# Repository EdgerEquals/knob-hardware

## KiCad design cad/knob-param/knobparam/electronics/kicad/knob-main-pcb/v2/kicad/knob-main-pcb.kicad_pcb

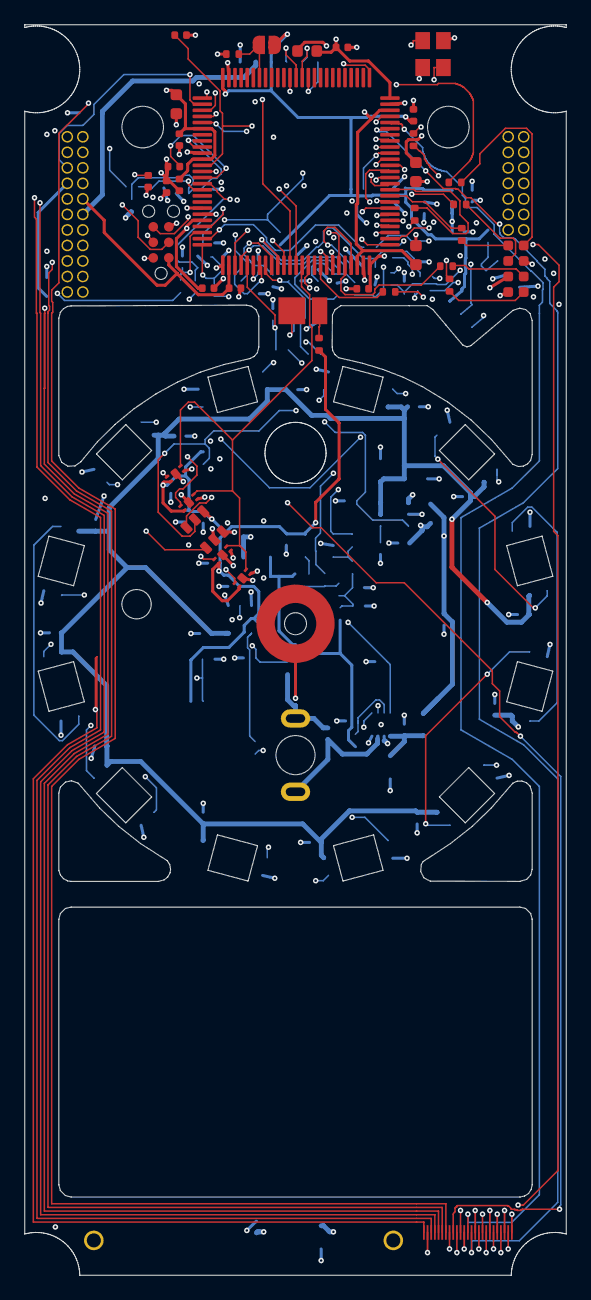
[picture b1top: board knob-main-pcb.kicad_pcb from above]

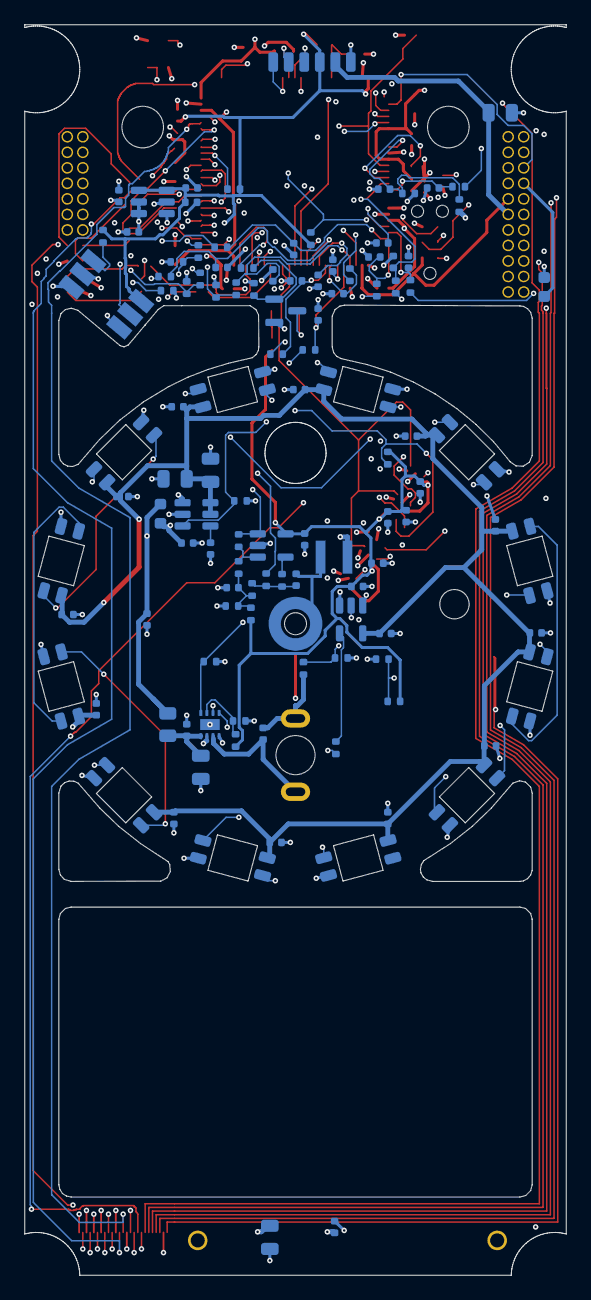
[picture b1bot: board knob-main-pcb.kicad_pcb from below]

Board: 6 copper layers, 44.3 x 102.3 mm, 156 parts (114 on the bottom side), 118 nets.

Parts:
C1, C2, C3, C4, C5, C10, C11, C12, C16, C18, C25, C27, C29, C31, C33, C44, C45, C46, C47, C48, C49, C50, C51, C52, C53, C54, C55, C56, C59, C60: 100nF; C_0402_1005Metric
C6, C64: 10uF; C_0603_1608Metric
C7, C8: 2.2uF; C_0603_1608Metric
C9, C15, C17, C40, C57: 1uF; C_0402_1005Metric
C13, C14: 15pF C0G; C_0402_1005Metric
C19, C20, C21, C22, C23, C24, C26, C28, C30, C32, C37, C38, C39, C41, C65: 1nF C0G; C_0402_1005Metric
C34, C36, C58: 100nF 16V; C_0402_1005Metric
C35, C42, C43, C63: 22uF 16V; C_0805_2012Metric
C61: 10uF 25V; C_0805_2012Metric
C62: 100nF 50V; C_0402_1005Metric
D1, D2, D3, D4, D5, D6, D7, D8, D9, D10, D11, D12: SK6812MINI-E; LED_SK6812MINI-E_Reverse
D13: JNJ-V-2835CW-665003-S-D1; LED_PLCC_2835
FB1: FCM1608KF-601T03; L_0603_1608Metric
FB2: BLM18KG121TZ1D; L_0603_1608Metric
H1: TubeRodClamp_M1.6; TubeRodClamp_Main_M1.6
J1: link flex pads; LinkFlex_MainBoard_Pads_25x0.3
J2: board L header 2x11 1.27 THT; VBoard_L_Header_2x11_P1.27_THT
J3: board R header 2x11 1.27 hybrid; VBoard_R_Header_2x11_P1.27_Hybrid
J4: TC2030-IDC-NL; Tag-Connect_TC2030-IDC-NL_2x03_P1.27mm_Vertical
J5: cover board pads; Pads_1x6_P1.27_SMD
JP1: BOOT0 to 3V3 (bridge to start the ROM bootloader); SolderJumper-2_P1.3mm_Open_RoundedPad1.0x1.5mm
L1: NR3015T470M; L_Taiyo-Yuden_NR-30xx
M1: 1220 coreless planetary, 6 V (hand-solder); Motor_1220_Tabs_Relief
MP1: post GND; Post_Pin_1.0
MP2: post VSYS; Post_Pin_1.0
Q1: 2N7002; SOT-23
R1, R23, R25, R26, R34, R40, R41, R42: 10k; R_0402_1005Metric
R2, R3, R38: 33R; R_0402_1005Metric
R4, R5, R6, R7, R8, R18, R19, R20, R21, R22, R27, R28, R33, R39, R47: 100R; R_0402_1005Metric
R9: 1M; R_0402_1005Metric
R10, R11, R44: 4.7k; R_0402_1005Metric
R12, R13, R14, R15, R16, R17: 22R; R_0402_1005Metric
R24, R46: 220R; R_0402_1005Metric
R29: 0R; R_0805_2012Metric
R30, R31: 0R; R_0402_1005Metric
R32: 3.3k 1%; R_0402_1005Metric
R35: 15k; R_0402_1005Metric
R36: 10k 1%; R_0402_1005Metric
R37, R48, R49: 100k; R_0402_1005Metric
R43: 1k; R_0402_1005Metric
R45: 47k; R_0402_1005Metric
R50: 27k; R_0402_1005Metric
RT1: 10k NTC B3380; R_0402_1005Metric
U1: STM32H743VIT6; LQFP-100_14x14mm_P0.5mm
U2: REF3430IDBVR; SOT-23-6
U3, U4, U5, U6: TMAG5253BA3IQDMRR; X2SON-4_TMAG5253
U7: TMAG5273A2QDBVR; SOT-23-6_TMAG5273_Tight
U8: EE-SX1321; Omron_EE-SX1321
U9: DRV8213DSGR; WSON-8-1EP_2x2mm_P0.5mm_EP0.9x1.6mm
U10: TPS22918DBVR; SOT-23-6
U11: SN74AHCT1G125DBVR; SOT-23-5
U12: TLV3601DBVR; SOT-23-5
Y1: 25MHz 12pF; Crystal_SMD_3225-4Pin_3.2x2.5mm

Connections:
3V3: C1.1, C2.1, C3.1, C4.1, C5.1, C6.1, C11.1, C15.1, C16.1, C25.1, C27.1, C29.1, C31.1, C33.1, C60.1, C64.1, FB1.1, J2.13, J2.15, J2.16, J3.20, J4.1, J5.4, JP1.2, R10.1, R11.1, R23.1, R24.1, R31.2, R36.1, R40.1, R46.1, U1.6, U1.11, U1.27, U1.50, U1.75, U1.100, U2.3, U2.4, U3.1, U4.1, U5.1, U6.1, U7.4, U8.6, U12.5
5V: C57.1, C63.1, FB2.1, J2.7, J2.9, J2.10, J2.11, J3.19, J5.5, L1.1, R29.1
5V_EN: J2.18, U1.2
AGND_SENSE: C23.1, R8.2, U1.29
AGND_SENSE_L: J1.24, R8.1, R9.1
AUDIO_IN: C22.1, R7.2, U1.24
AUDIO_IN_L: J1.22, R7.1
AUDIO_OUT: J1.20, U1.28
BOOT0: JP1.1, R1.1, U1.94
BUS_PRESENT: C65.1, R49.2, R50.1, U1.9
CAN_RX: J3.16, U1.51
CAN_STBY: J3.17, U1.68
CAN_TX: J3.15, U1.52
COVER_EN: J5.3, U1.88
COVER_RX: J5.2, U1.87
COVER_TX: J5.1, U1.86
CS_DAC: J1.4, U1.37
CS_OLED: J1.5, U1.38
CV_IN1: C19.1, R4.2, U1.35
CV_IN1_L: J1.16, R4.1
CV_IN2: C20.1, R5.2, U1.34
CV_IN2_L: J1.17, R5.1
CV_IN3: C21.1, R6.2, U1.33
CV_IN3_L: J1.18, R6.1
DIAL_BUS: C58.2, R39.2, R42.1, R43.1
DIAL_CMN: R43.2, U12.4
DIAL_CMP: R44.2, R45.2, U12.3
DIAL_MID: C59.1, R40.2, R41.1, R42.2, R44.1
DIAL_RX: R45.1, U1.44, U12.1
DIAL_TX: R39.1, U1.43
ENC_A: R27.2, U1.63
ENC_A_L: R25.1, R27.1, U8.5
ENC_B: R28.2, U1.64
ENC_B_L: R26.1, R28.1, U8.4
ENC_LED: R24.2, U8.1
GAINSEL: R30.1, R31.1, U9.7
GND: C1.2, C2.2, C3.2, C4.2, C5.2, C6.2, C7.2, C8.2, C9.2, C10.2, C11.2, C12.2, C13.2, C14.2, C15.2, C16.2, C17.2, C18.2, C19.2, C20.2, C21.2, C22.2, C23.2, C24.2, C25.2, C26.2, C27.2, C28.2, C29.2, C30.2, C31.2, C32.2, C33.2, C34.2, C35.2, C37.2, C38.2, C39.2, C40.2, C41.2, C42.2, C43.2, C44.2, C45.2, C46.2, C47.2, C48.2, C49.2, C50.2, C51.2, C52.2, C53.2, C54.2, C55.2, C56.2, C57.2, C59.2, C60.2, C61.2, C62.2, C63.2, C64.2, C65.2, D1.3, D2.3, D3.3, D4.3, D5.3, D6.3, D7.3, D8.3, D9.3, D10.3, D11.3, D12.3, H1.1, J1.2, J1.12, J1.15, J1.19, J1.21, J1.23, J1.25, J2.2, J2.4, J2.6, J2.8, J2.12, J2.14, J2.17, J2.19, J2.21, J2.22, J3.1, J3.3, J3.6, J3.9, J3.14, J3.18, J3.21, J3.22, J4.5, J5.6, MP1.1, Q1.2, R1.2, R9.2, R25.2, R26.2, R30.2, R32.2, R35.2, R37.2, R41.2, R48.2, R50.2, RT1.2, U1.10, U1.19, U1.26, U1.49, U1.74, U1.99, U2.1, U2.2, U3.2, U3.5, U4.2, U4.5, U5.2, U5.5, U6.2, U6.5, U7.2, U7.3, U8.2, U8.3, U9.4, U9.9, U10.2, U11.1, U11.3, U12.2, Y1.2, Y1.4
HALL1: C26.1, R19.2, U1.32
HALL1_L: R19.1, U3.4
HALL2: C28.1, R20.2, U1.25
HALL2_L: R20.1, U4.4
HALL3D_INT: R23.2, U1.40, U7.5
HALL4: C30.1, R21.2, U1.23
HALL4_L: R21.1, U5.4
HALL5: C32.1, R22.2, U1.15
HALL5_L: R22.1, U6.4
HALL_EN: U1.39, U3.3, U4.3, U5.3, U6.3
HSE_IN: C13.1, U1.12, Y1.1
HSE_OUT: C14.1, U1.13, Y1.3
I2C_SCL: J1.8, R10.2, U1.67, U7.1
I2C_SDA: J1.9, R11.2, U1.66, U7.6
IO_INT: J1.10, U1.54
IPROPI: R32.1, R33.1, U9.8
JOY_LADDER: C24.1, R18.2, U1.16
JOY_LADDER_L: J2.20, R18.1
JOY_PWR_EN: J3.13, U1.65
JOY_QSPI_CLK: R12.1, U1.36
JOY_QSPI_IO0: R14.1, U1.58
JOY_QSPI_IO1: R15.1, U1.59
JOY_QSPI_IO2: R16.1, U1.1
JOY_QSPI_IO3: R17.1, U1.60
JOY_QSPI_NCS: R13.1, U1.46
JOY_RST: J3.11, U1.57
JOY_TE: J3.12, U1.56
LIGHT_A: D13.2, R46.2
LIGHT_G: Q1.1, R47.2, R48.1
LIGHT_K: D13.1, Q1.3
LINK_MOSI: R3.1, U1.5
LINK_SCK: R2.1, U1.42
MIDI_TX: J1.11, U1.55
MOSI_L: J1.3, R3.2
MOT_A: C36.1, M1.1, R34.1, U9.2
MOT_B: C36.2, M1.2, U9.3
MOT_IN1: U1.61, U9.6
MOT_IN2: U1.62, U9.5
MOT_SENSE: C37.1, R33.2, U1.30
MOT_VOICE: C38.1, R34.2, R35.1, U1.31
NRST: C12.1, J4.3, U1.14
NTC: C39.1, R36.2, RT1.1, U1.22
OLED_DC: J1.6, U1.4
OLED_RES: J1.7, U1.3
PWR_LIGHT: R47.1, U1.47
QSPI_CLK_R: J3.2, R12.2
QSPI_IO0_R: J3.5, R14.2
QSPI_IO1_R: J3.7, R15.2
QSPI_IO2_R: J3.8, R16.2
QSPI_IO3_R: J3.10, R17.2
QSPI_NCS_R: J3.4, R13.2
RGB_DIN: U1.53, U11.2
RGB_EN: R37.1, U1.45, U10.3
RING_5V: C42.1, C43.1, C44.1, C45.1, C46.1, C47.1, C48.1, C49.1, C50.1, C51.1, C52.1, C53.1, C54.1, C55.1, C56.1, D1.1, D2.1, D3.1, D4.1, D5.1, D6.1, D7.1, D8.1, D9.1, D10.1, D11.1, D12.1, U10.5, U10.6, U11.5
RING_CT: C41.1, U10.4
RING_D0: D1.4, R38.2
RING_D1: D1.2, D2.4
RING_D2: D2.2, D3.4
RING_D3: D3.2, D4.4
RING_D4: D4.2, D5.4
RING_D5: D5.2, D6.4
RING_D6: D6.2, D7.4
RING_D7: D7.2, D8.4
RING_D8: D8.2, D9.4
RING_D9: D9.2, D10.4
RING_D10: D10.2, D11.4
RING_D11: D11.2, D12.4
RING_DY: R38.1, U11.4
RING_IN: C40.1, FB2.2, U10.1
ROD: C58.1, H1.2, L1.2
SCK_L: J1.1, R2.2
SWCLK: J4.4, U1.76
SWDIO: J4.2, U1.72
SWO: J4.6, U1.89
USB_DM: J1.14, U1.70
USB_DP: J1.13, U1.71
VCAP: C7.1, C8.1, U1.48, U1.73
VDDA: C9.1, C10.1, FB1.2, U1.21
VM: C34.1, C35.1, R29.2, U9.1
VREFP: C17.1, C18.1, U1.20, U2.5, U2.6
VSYS: C61.1, C62.1, J2.1, J2.3, J2.5, MP2.1, R49.1

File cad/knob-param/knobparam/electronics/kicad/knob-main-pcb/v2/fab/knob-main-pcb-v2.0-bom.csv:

Item,Designator,Qty,Value,Footprint,Manufacturer,MPN,LCSC,Datasheet
1,"C13,C14",2,15pF C0G,C_0402_1005Metric,,,,
2,"C1,C10,C11,C12,C16,C18,C2,C25,C27,C29,C3,C31,C33,C4,C44,C45,C46,C47,C48,C49,C5,C50,C51,C52,C53,C54,C55,C56,C59,C60",30,100nF,C_0402_1005Metric,,,,
3,"C19,C20,C21,C22,C23,C24,C26,C28,C30,C32,C37,C38,C39",13,1nF C0G,C_0402_1005Metric,,,,
4,"C34,C36,C58",3,100nF 16V,C_0402_1005Metric,,,,
5,"C40,C57",2,1uF 10V,C_0402_1005Metric,,,,
6,"C41,C65",2,1nF,C_0402_1005Metric,,,,
7,"C35,C42,C43,C63",4,22uF 10V,C_0805_2012Metric,,,,
8,"C6,C64",2,10uF,C_0603_1608Metric,,,,
9,C61,1,10uF 25V,C_0805_2012Metric,,,,
10,C62,1,100nF 25V,C_0402_1005Metric,,,,
11,"C7,C8",2,2.2uF,C_0603_1608Metric,,,,
12,"C15,C17,C9",3,1uF,C_0402_1005Metric,,,,
13,D13,1,JNJ-V-2835CW-665003-S-D1,LED_PLCC_2835,,JNJ-V-2835CW-665003-S-D1,C42375664,https://www.lcsc.com/product-detail/C42375664.html
14,"D1,D10,D11,D12,D2,D3,D4,D5,D6,D7,D8,D9",12,SK6812MINI-E,LED_SK6812MINI-E_Reverse,,SK6812MINI-E,C5149201,https://www.lcsc.com/product-detail/C5149201.html
15,FB1,1,FCM1608KF-601T03,L_0603_1608Metric,,FCM1608KF-601T03,C141723,https://www.lcsc.com/product-detail/C141723.html
16,FB2,1,BLM18KG121TZ1D,L_0603_1608Metric,,BLM18KG121TZ1D,C396652,https://www.lcsc.com/product-detail/C396652.html
17,J2,1,board L header 2x11 1.27 THT,VBoard_L_Header_2x11_P1.27_THT,,,,
18,J3,1,board R header 2x11 1.27 hybrid,VBoard_R_Header_2x11_P1.27_Hybrid,,,,
19,L1,1,NR3015T470M,L_Taiyo-Yuden_NR-30xx,,NR3015T470M,C87171,https://www.lcsc.com/product-detail/C87171.html
20,Q1,1,2N7002,SOT-23,,2N7002,C8545,https://www.lcsc.com/product-detail/C8545.html
21,"R1,R23,R25,R26,R34,R40,R41,R42",8,10k,R_0402_1005Metric,,,,
22,"R12,R13,R14,R15,R16,R17",6,22R,R_0402_1005Metric,,,,
23,"R18,R19,R20,R21,R22,R27,R28,R33,R39,R4,R47,R5,R6,R7,R8",15,100R,R_0402_1005Metric,,,,
24,"R2,R3,R38",3,33R,R_0402_1005Metric,,,,
25,R29,1,0R,R_0805_2012Metric,,,,
26,R30,1,0R,R_0402_1005Metric,,,,
27,R32,1,3.3k 1%,R_0402_1005Metric,,,,
28,R35,1,15k,R_0402_1005Metric,,,,
29,R36,1,10k 1%,R_0402_1005Metric,,,,
30,R43,1,1k,R_0402_1005Metric,,,,
31,R44,1,4.7k,R_0402_1005Metric,,,,
32,R45,1,47k,R_0402_1005Metric,,,,
33,"R24,R46",2,220R,R_0402_1005Metric,,,,
34,"R37,R48,R49",3,100k,R_0402_1005Metric,,,,
35,R50,1,27k,R_0402_1005Metric,,,,
36,R9,1,1M,R_0402_1005Metric,,,,
37,RT1,1,10k NTC B3380,R_0402_1005Metric,,NCP15XH103F03RC,C77131,https://www.lcsc.com/product-detail/C77131.html
38,U1,1,STM32H743VIT6,LQFP-100_14x14mm_P0.5mm,,STM32H743VIT6,C114409,https://www.st.com/resource/en/datasheet/stm32h743vi.pdf
39,U10,1,TPS22918DBVR,SOT-23-6,,TPS22918DBVR,C131941,https://www.ti.com/lit/gpn/tps22918
40,U11,1,SN74AHCT1G125DBVR,SOT-23-5,,SN74AHCT1G125DBVR,C7484,https://www.ti.com/lit/gpn/sn74ahct1g125
41,U12,1,TLV3601DBVR,SOT-23-5,,TLV3601DBVR,C5213958,https://www.ti.com/lit/gpn/TLV3601
42,U2,1,REF3430IDBVR,SOT-23-6,,REF3430IDBVR,C2156866,https://www.ti.com/lit/gpn/REF34
43,"U3,U4,U5,U6",4,TMAG5253BA3IQDMRR,X2SON-4_TMAG5253,,TMAG5253BA3IQDMRR,C22401868,https://www.ti.com/lit/gpn/tmag5253
44,U7,1,TMAG5273A2QDBVR,SOT-23-6_TMAG5273_Tight,,TMAG5273A2QDBVR,C3715882,https://www.ti.com/lit/gpn/tmag5273
45,U8,1,EE-SX1321,Omron_EE-SX1321,,EE-SX1321,C469128,https://www.lcsc.com/product-detail/C469128.html
46,U9,1,DRV8213DSGR,WSON-8-1EP_2x2mm_P0.5mm_EP0.9x1.6mm,,DRV8213DSGR,C22407186,https://www.ti.com/lit/gpn/drv8213
47,Y1,1,25MHz 12pF,Crystal_SMD_3225-4Pin_3.2x2.5mm,,X322525MOB4SI,C9006,https://www.lcsc.com/product-detail/C9006.html

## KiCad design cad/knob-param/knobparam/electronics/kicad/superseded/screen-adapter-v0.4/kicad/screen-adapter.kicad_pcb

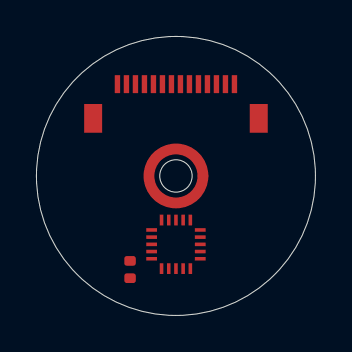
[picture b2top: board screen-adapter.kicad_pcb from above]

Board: 2 copper layers, 15.5 x 15.5 mm, 4 parts (0 on the bottom side), 2 nets, no tracks yet.

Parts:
C1: TubeRodClamp_Adapter_M1.6
C2: 100n; C_0402
J1: Z07101-P14 (FPC 14P 0.5); FPC_14P_0.5mm_Top
U1: CH32V003F4U6; QFN-20_3x3_P0.4_CH32V003

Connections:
GND: C1.1, C2.2, U1.4
VCC: C2.1, U1.6

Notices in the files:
parts and their libraries:
SK6812MINI-E reverse mount; pads after marbastlib (CERN-OHL-P) and Keebio-Parts (MIT)
ring site 6/12; pads after Keebio-Parts (MIT) and marbastlib (CERN-OHL-P) [S]; MSL 5a; [C] pin order against the datasheet drawing of the revision LCSC ships
